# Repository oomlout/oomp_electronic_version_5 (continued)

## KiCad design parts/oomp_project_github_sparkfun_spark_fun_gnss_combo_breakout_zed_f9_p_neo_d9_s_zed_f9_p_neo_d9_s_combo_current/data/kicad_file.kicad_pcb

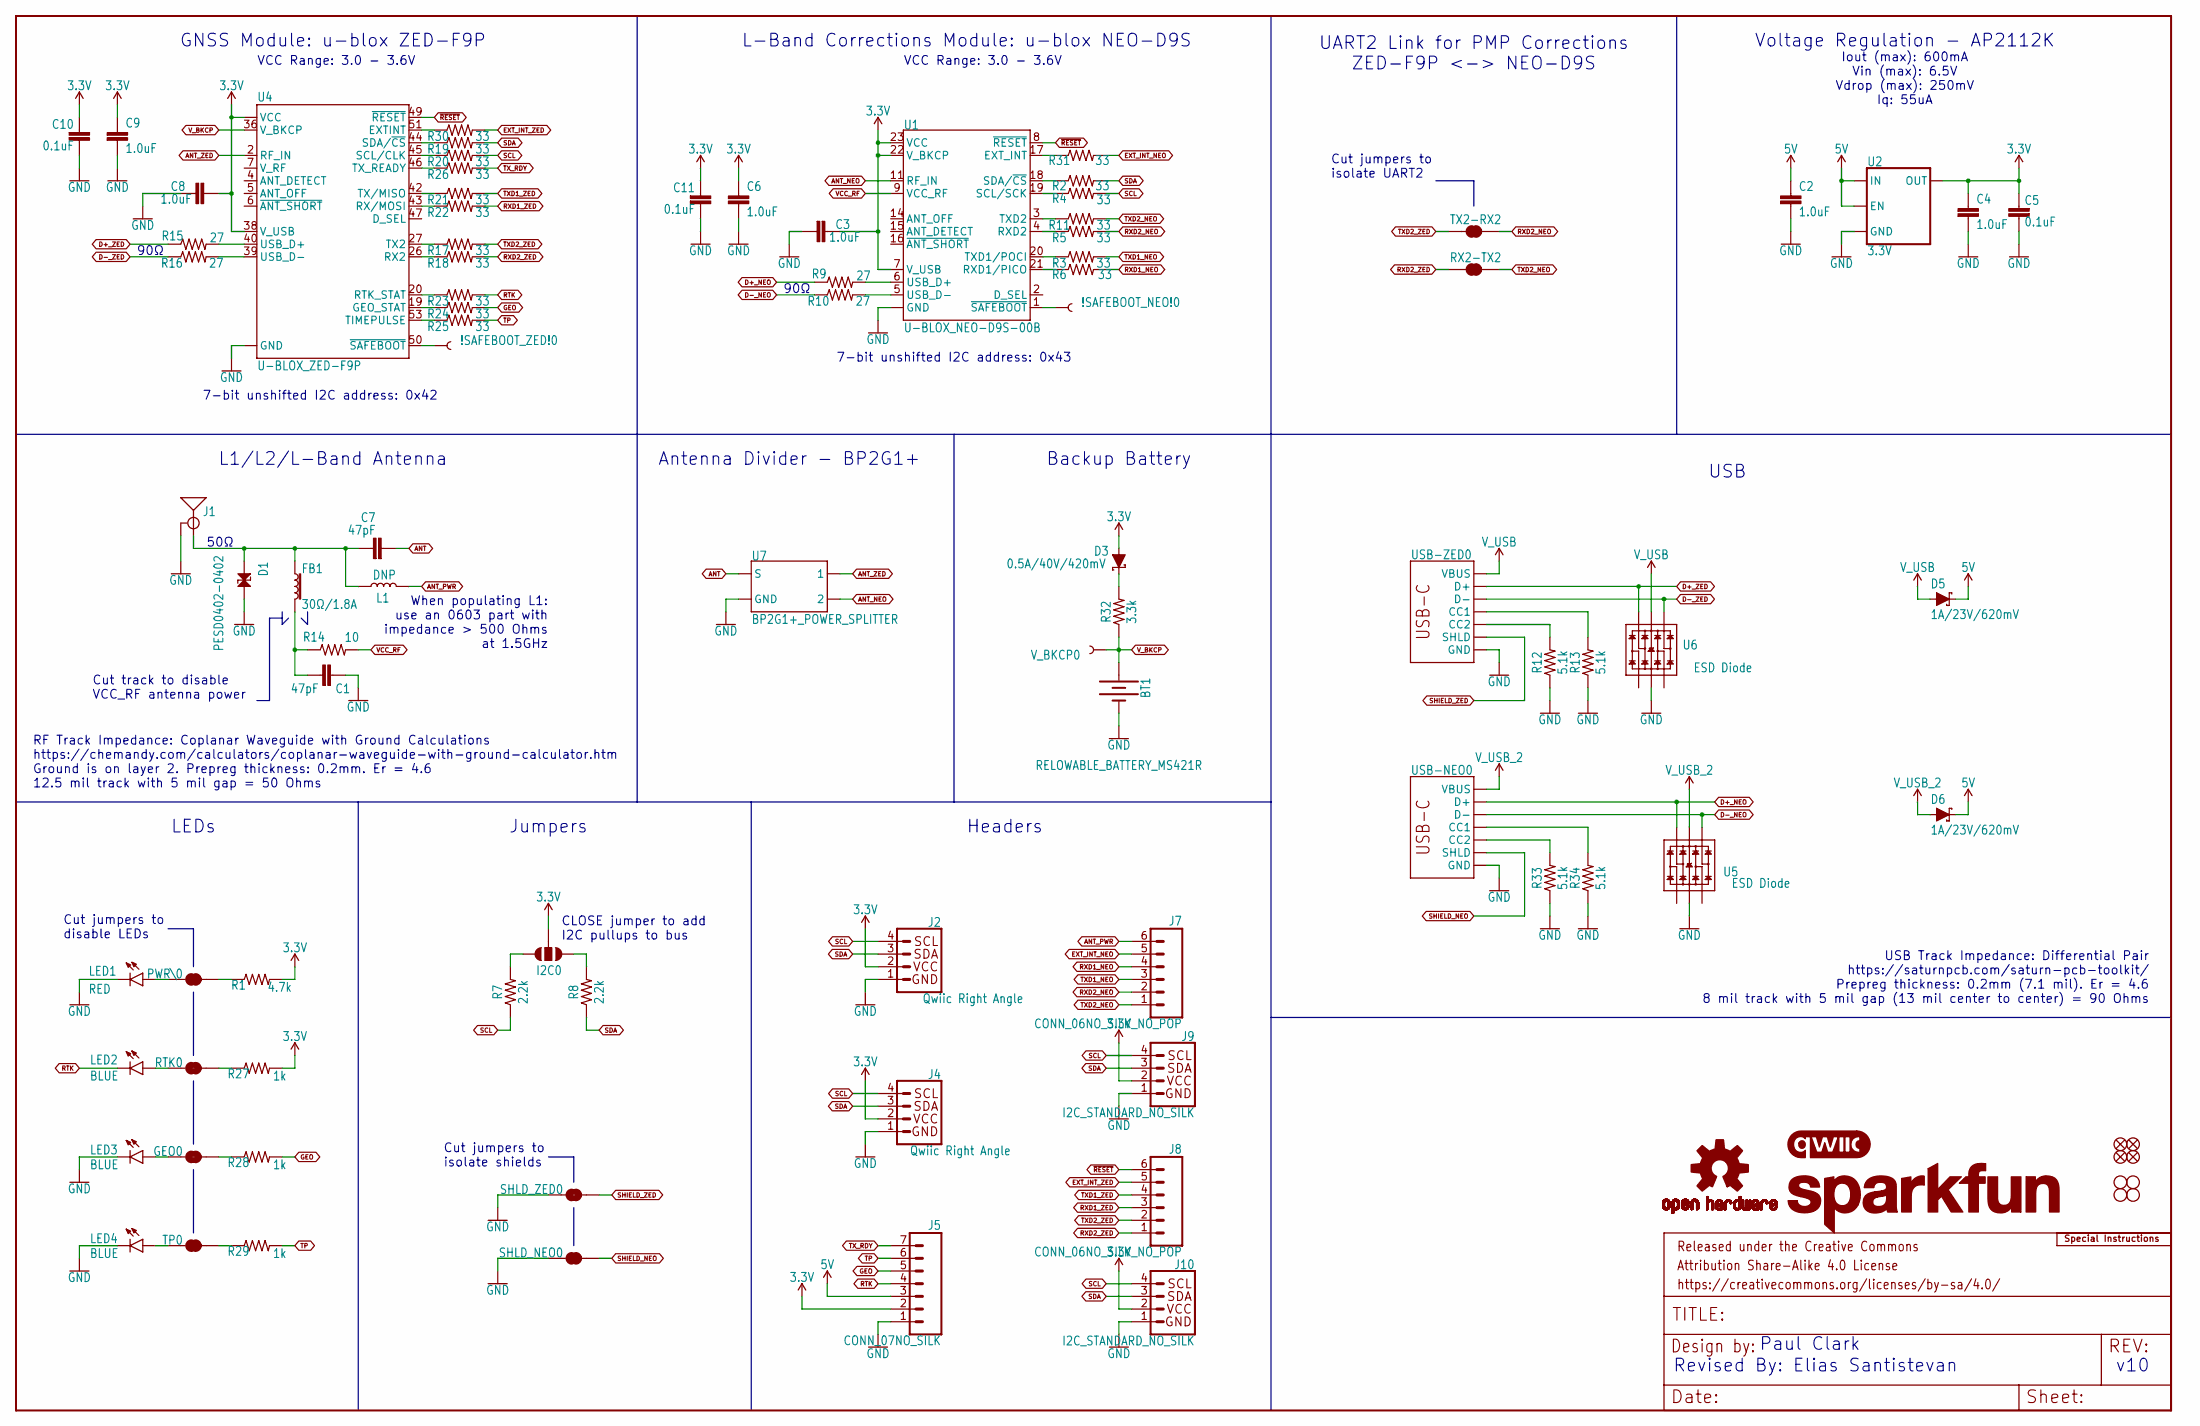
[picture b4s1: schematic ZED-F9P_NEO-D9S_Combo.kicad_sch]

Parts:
!SAFEBOOT_NEO!0: TEST-POINTPOGO_PTH; 1X01_NO_SILK
!SAFEBOOT_ZED!0: TEST-POINTPOGO_PTH; 1X01_NO_SILK
BT1: RELOWABLE_BATTERY_MS421R; MS421R_IV03E
C1, C7: 47pF; 0603
C2, C3, C4, C6, C8, C9: 1.0uF; 0603
C5, C10, C11: 0.1uF; 0603
D1: PESD0402-0402; 0402; MOUSE_PART 650-PESD0402-140; DIGIKEY_PART PESD0402-140CT-ND
D3: 0.5A/40V/420mV; SOD-323
D5, D6: 1A/23V/620mV; SOD-323
FB1: 30Ω/1.8A; 0603
FRAME2: FRAME-LEDGER; CREATIVE_COMMONS
GEO0: JUMPER-SMT_2_NC_TRACE_SILK; SMT-JUMPER_2_NC_TRACE_SILK
I2C0: JUMPER-SMT_3_NO_SILK; SMT-JUMPER_3_NO_SILK
J1: ANTENNA-SMA-GROUNDEDEDGE_SMA; SMA-EDGE
J2, J4: Qwiic Right Angle; JST04_1MM_RA
J5: CONN_07NO_SILK; 1X07_NO_SILK
J7, J8: CONN_06NO_SILK_NO_POP; 1X06_NO_SILK
J9, J10: I2C_STANDARD_NO_SILK; 1X04_NO_SILK
JP21, JP61, JP71, JP81: FIDUCIALUFIDUCIAL; MICRO-FIDUCIAL
JP31, JP41, JP91, JP101: STAND-OFF
L1: DNP; 0603_NO-CREAM
LED1: RED; LED-0603
LED2, LED3, LED4: BLUE; LED-0603
LOGO2: SFE_LOGO_NAME.1_INCH; SFE_LOGO_NAME_.1
LOGO3: QWIIC_LOGO_5MM; QWIIC_5MM
LOGO4: OSHW-LOGOS; OSHW-LOGO-S
LOGO5: SPECIAL_INSTRUCTIONS-ORDERING; ORDERING_INSTRUCTIONS
PWR\0: JUMPER-SMT_2_NC_TRACE_SILK; SMT-JUMPER_2_NC_TRACE_SILK
R1: 4.7k; 0603
R2, R3, R4, R5, R6, R11, R17, R18, R19, R20, R21, R22, R23, R24, R25, R26, R30, R31: 33; 0603
R7, R8: 2.2k; 0603
R9, R10, R15, R16: 27; 0603
R12, R13, R33, R34: 5.1k; 0603
R14: 10; 0603
R27, R28, R29: 1k; 0603
R32: 3.3k; 0603
RTK0: JUMPER-SMT_2_NC_TRACE_SILK; SMT-JUMPER_2_NC_TRACE_SILK
RX2-TX2: JUMPER-SMT_2_NC_TRACE_SILK; SMT-JUMPER_2_NC_TRACE_SILK
SHLD_NEO0: JUMPER-SMT_2_NC_TRACE_SILK; SMT-JUMPER_2_NC_TRACE_SILK
SHLD_ZED0: JUMPER-SMT_2_NC_TRACE_SILK; SMT-JUMPER_2_NC_TRACE_SILK
TP0: JUMPER-SMT_2_NC_TRACE_SILK; SMT-JUMPER_2_NC_TRACE_SILK
TX2-RX2: JUMPER-SMT_2_NC_TRACE_SILK; SMT-JUMPER_2_NC_TRACE_SILK
U1: U-BLOX_NEO-D9S-00B; NEO-M9N_M8T_M8U_D9S
U2: 3.3V; SOT23-5
U4: U-BLOX_ZED-F9P; ZED-F9P
U5, U6: ESD Diode; SOT-23-6
U7: BP2G1+_POWER_SPLITTER; XX21
USB-NEO0: USB Female Type C Connector; USB-C-16P_4LAYER-PADS
USB-ZED0: USB Female Type C Connector; USB-C-16P_4LAYER-PADS
V_BKCP0: TEST-POINT3X5; PAD.03X.05

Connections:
3.3V: C3.1, C4.1, C5.2, C6.1, C8.2, C9.1, C10.2, C11.2, D3.A, I2C0.2, J2.2, J4.2, J5.2, J9.2, J10.2, R1.2, R27.2, U1.7 (V_USB), U1.22 (V_BKCP), U1.23 (VCC), U2.5 (OUT), U4.33 (VCC), U4.34 (VCC), U4.38 (V_USB)
5V: C2.1, D5.C, D6.C, J5.3, U2.1 (IN), U2.3 (EN)
ANT: C7.2, U7.2 (S)
ANT_NEO: U1.11 (RF_IN), U7.5 (2)
ANT_PWR: J7.6, L1.2
ANT_VCC: C1.1, FB1.2, R14.1
ANT_ZED: U4.2 (RF_IN), U7.8 (1)
D+_NEO: R9.1, U5.6 (IO4), USB-NEO0.A6 (D+), USB-NEO0.B6 (D+)
D+_ZED: R15.1, U6.6 (IO4), USB-ZED0.A6 (D+), USB-ZED0.B6 (D+)
D-_NEO: R10.1, U5.4 (IO3), USB-NEO0.A7 (D-), USB-NEO0.B7 (D-)
D-_ZED: R16.1, U6.4 (IO3), USB-ZED0.A7 (D-), USB-ZED0.B7 (D-)
EXT_INT_NEO: J7.5, R31.2
EXT_INT_ZED: J8.5, R30.2
GEO: J5.5, R24.2, R28.2
GND: BT1.-, C1.2, C2.2, C3.2, C4.2, C5.1, C6.2, C8.1, C9.2, C10.1, C11.1, D1.2, J1.GND@0 (GND), J1.GND@1 (GND), J1.GND@2 (GND), J1.GND@3 (GND), J2.1, J4.1, J5.1, J9.1, J10.1, LED1.C, LED3.C, LED4.C, R12.1, R13.1, R33.1, R34.1, SHLD_NEO0.1, SHLD_ZED0.1, U1.10 (GND), U1.12 (GND), U1.13 (GND), U1.24 (GND), U2.2 (GND), U4.1 (GND), U4.3 (GND), U4.12 (GND), U4.14 (GND), U4.32 (GND), U4.37 (GND), U4.41 (GND), U4.48 (GND), U4.55 (GND), U4.56 (GND), U4.57 (GND), U4.58 (GND), U4.59 (GND), U4.60 (GND), U4.61 (GND), U4.62 (GND), U4.63 (GND), U4.64 (GND), U4.65 (GND), U4.66 (GND), U4.67 (GND), U4.68 (GND), U4.69 (GND), U4.70 (GND), U4.71 (GND), U4.72 (GND), U4.73 (GND), U4.74 (GND), U4.75 (GND), U4.76 (GND), U4.77 (GND), U4.78 (GND), U4.79 (GND), U4.80 (GND), U4.81 (GND), U4.82 (GND), U4.83 (GND), U4.84 (GND), U4.85 (GND), U4.86 (GND), U4.87 (GND), U4.88 (GND), U4.89 (GND), U4.90 (GND), U4.91 (GND), U4.92 (GND), U4.93 (GND), U4.94 (GND), U4.95 (GND), U4.96 (GND), U4.97 (GND), U4.98 (GND), U4.99 (GND), U4.100 (GND), U4.101 (GND), U4.102 (GND), U5.2 (VSS), U6.2 (VSS), U7.1 (GND), U7.3 (GND), U7.4 (GND), U7.6 (GND), U7.7 (GND), USB-NEO0.GND, USB-NEO0.GND2 (GND), USB-ZED0.GND, USB-ZED0.GND2 (GND)
unnamed: PWR\0.2, R1.1
unnamed: R3.1, U1.20 (TXD1/POCI)
unnamed: R2.1, U1.18 (SDA/~CS)
unnamed: R4.1, U1.19 (SCL/SCK)
unnamed: I2C0.1, R8.2
unnamed: R6.1, U1.21 (RXD1/PICO)
unnamed: R12.2, USB-ZED0.B5 (CC2)
unnamed: I2C0.3, R7.2
unnamed: R13.2, USB-ZED0.A5 (CC1)
unnamed: LED1.A, PWR\0.1
unnamed: R9.2, U1.6 (USB_D+)
unnamed: R10.2, U1.5 (USB_D-)
unnamed: D3.C, R32.2
unnamed: R11.1, U1.3 (TXD2)
unnamed: R5.1, U1.4 (RXD2)
unnamed: R15.2, U4.40 (USB_D+)
unnamed: R16.2, U4.39 (USB_D-)
unnamed: R19.1, U4.44 (SDA/~CS)
unnamed: R20.1, U4.45 (SCL/CLK)
unnamed: R21.1, U4.42 (TX/MISO)
unnamed: R22.1, U4.43 (RX/MOSI)
unnamed: R26.1, U4.46 (TX_READY)
unnamed: LED2.A, RTK0.1
unnamed: R17.1, U4.27 (TX2)
unnamed: R18.1, U4.26 (RX2)
unnamed: GEO0.1, LED3.A
unnamed: LED4.A, TP0.1
unnamed: R27.1, RTK0.2
unnamed: GEO0.2, R28.1
unnamed: R29.1, TP0.2
unnamed: R30.1, U4.51 (EXTINT)
unnamed: R31.1, U1.17 (EXT_INT)
unnamed: R33.2, USB-NEO0.B5 (CC2)
unnamed: R34.2, USB-NEO0.A5 (CC1)
unnamed: R23.1, U4.20 (RTK_STAT)
unnamed: R24.1, U4.19 (GEO_STAT)
unnamed: R25.1, U4.53 (TIMEPULSE)
RTK: J5.4, LED2.C, R23.2
RXD1_NEO: J7.4, R6.2
RXD1_ZED: J8.3, R22.2
RXD2_NEO: J7.2, R5.2, TX2-RX2.2
RXD2_ZED: J8.1, R18.2, RX2-TX2.1
SCL: J2.4, J4.4, J9.4, J10.4, R4.2, R7.1, R20.2
SDA: J2.3, J4.3, J9.3, J10.3, R2.2, R8.1, R19.2
SHIELD_NEO: SHLD_NEO0.2, USB-NEO0.SHLD1 (SHLD), USB-NEO0.SHLD2 (SHLD), USB-NEO0.SHLD3 (SHLD), USB-NEO0.SHLD4 (SHLD)
SHIELD_ZED: SHLD_ZED0.2, USB-ZED0.SHLD1 (SHLD), USB-ZED0.SHLD2 (SHLD), USB-ZED0.SHLD3 (SHLD), USB-ZED0.SHLD4 (SHLD)
SMA: C7.1, D1.1, FB1.1, J1.SIG (SIGNAL), L1.1
TP: J5.6, R25.2, R29.2
TXD1_NEO: J7.3, R3.2
TXD1_ZED: J8.4, R21.2
TXD2_NEO: J7.1, R11.2, RX2-TX2.2
TXD2_ZED: J8.2, R17.2, TX2-RX2.1
TX_RDY: J5.7, R26.2
VCC_RF: R14.2, U1.9 (VCC_RF)
V_BKCP: BT1.+, R32.1, U4.36 (V_BKCP), V_BKCP0.1
V_USB: D5.A, U6.5 (VCC), USB-ZED0.VBUS1 (VBUS), USB-ZED0.VBUS2 (VBUS)
V_USB_2: D6.A, U5.5 (VCC), USB-NEO0.VBUS1 (VBUS), USB-NEO0.VBUS2 (VBUS)
~RESET: J8.6, U1.8 (~RESET), U4.49 (~RESET)
~SAFEBOOT_NEO: !SAFEBOOT_NEO!0.1, U1.1 (~SAFEBOOT)
~SAFEBOOT_ZED: !SAFEBOOT_ZED!0.1, U4.50 (~SAFEBOOT)

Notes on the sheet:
Cut jumpers to isolate shields
CLOSE jumper to add I2C pullups to bus
Paul Clark
v10
Headers
Jumpers
When populating L1: use an 0603 part with impedance > 500 Ohms at 1.5GHz
7-bit unshifted I2C address: 0x42
L-Band Corrections Module: u-blox NEO-D9S
50Ω
UART2 Link for PMP Corrections ZED-F9P <-> NEO-D9S
90Ω
Revised By: Elias Santistevan
VCC Range: 3.0 - 3.6V
Voltage Regulation - AP2112K
Iout (max): 600mA Vin (max): 6.5V Vdrop (max): 250mV Iq: 55uA
Backup Battery
Cut jumpers to isolate UART2
7-bit unshifted I2C address: 0x43
Antenna Divider - BP2G1+
LEDs
USB Track Impedance: Differential Pair https://saturnpcb.com/saturn-pcb-toolkit/ Prepreg thickness: 0.2mm (7.1 mil). Er = 4.6 8 mil track with 5 mil gap (13 mil center to center) = 90 Ohms
RF Track Impedance: Coplanar Waveguide with Ground Calculations https://chemandy.com/calculators/coplanar-waveguide-with-ground-calculator.htm Ground is on layer 2. Prepreg thickness: 0.2mm. Er = 4.6 12.5 mil track with 5 mil gap = 50 Ohms
Cut track to disable VCC_RF antenna power
USB
L1/L2/L-Band Antenna
Cut jumpers to disable LEDs
GNSS Module: u-blox ZED-F9P

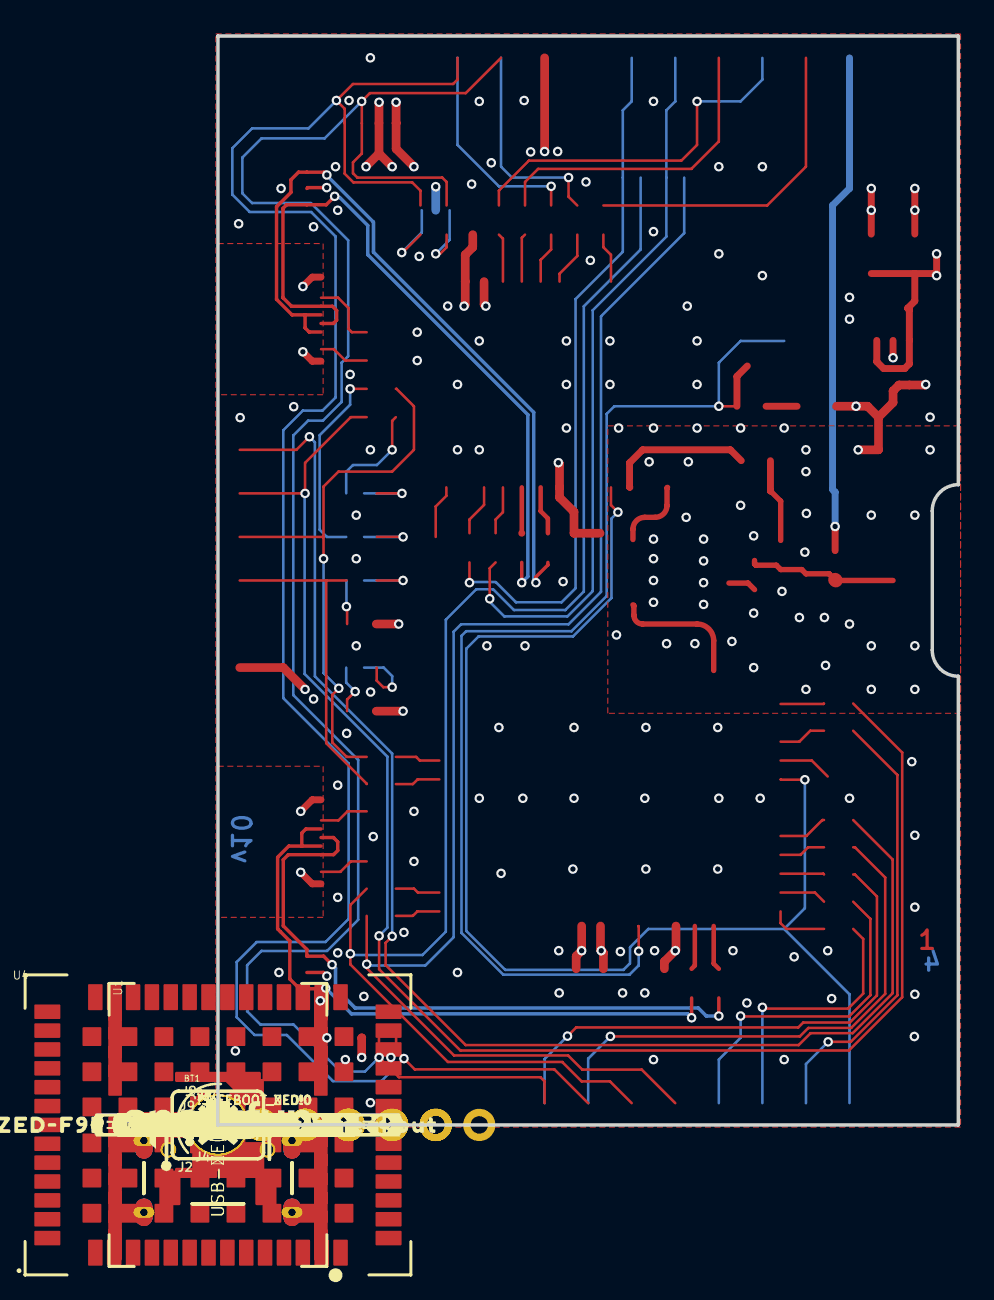
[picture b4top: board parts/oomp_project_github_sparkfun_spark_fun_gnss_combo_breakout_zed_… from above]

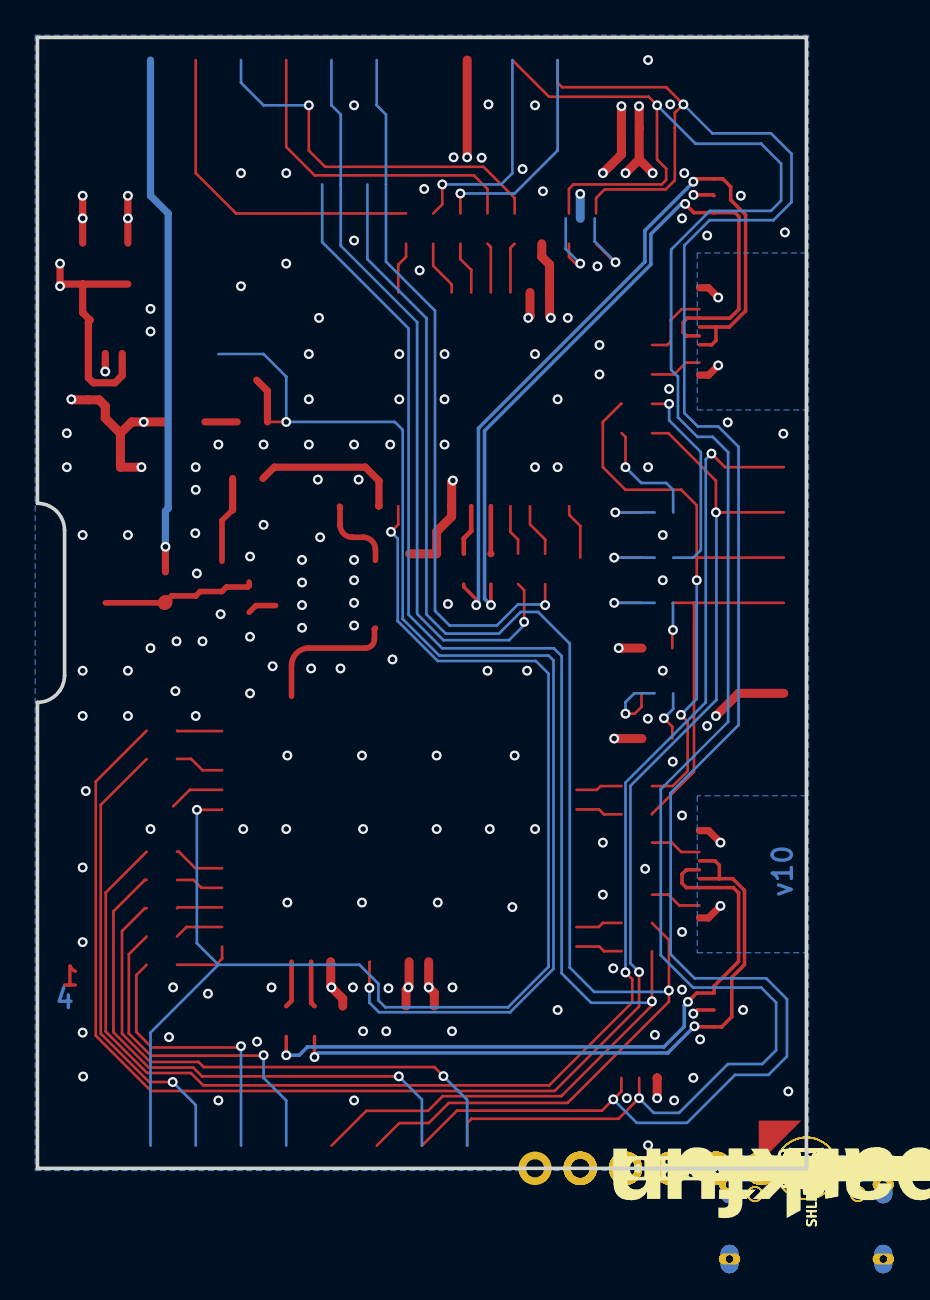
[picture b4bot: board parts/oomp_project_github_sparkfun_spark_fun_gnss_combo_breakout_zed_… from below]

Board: 4 copper layers, 43.2 x 63.5 mm, 179 parts (60 on the bottom side), 75 nets.

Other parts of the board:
LOGO1: OSHW-LOGOS; OSHW-LOGO-S
LOGO6: QWIIC_LOGO_5MM; QWIIC_5MM
U$1, U$2, U$3: #GND#0
U$4, U$5, U$6: #GND#1
U$7: #SHLD_ZED#15
U$8, U$10: #SDA#0
U$9, U$13: #SCL#0
U$11, U$12: #SDA#1
U$14: L#BAND18
U$15, U$30: #SCL#1
U$16: #RTK#0
U$17: #RTK#1
U$18: #GEO#0
U$19: #GEO#1
U$20: #5V#0
U$21: #5V#6
U$22, U$23, U$56: #3V3#0
U$24, U$25, U$70: #3V3#4
U$26: #TP#0
U$27: #TP#1
U$28: #TX_RDY#0
U$29: #TX_RDY#1
U$31, U$39, U$40: #TX2#0
U$32, U$34, U$35: #RX2#0
U$33: L1#L218
U$36, U$37: #RX2#3
U$41, U$42: #TX2#3
U$43, U$44: #RX1#0
U$45: ##RESET##0
U$46: ##RESET##1
U$47: #EXT_INT#0
U$48: #EXT_INT_ZED#0
U$49, U$50: #RX1#2
U$51, U$57: #TX1#0
U$52: #I�C#0
U$53: #SHLD_NEO#12
U$54: ANTENNA18
U$55: NEO#D9S16
U$58: #ANT_PWR#0
U$59: #ANT_PWR#1
U$60, U$61: #TX1#2
U$62: #EXT_INT_NEO#0
U$63: #EXT_INT_NEO#1
U$64: COMBO16
U$65: ZED#F9P10
U$66: NEO#D9S10
U$67: BREAKOUT17
U$68: SFE_LOGO_NAME_.2
U$69: #PWR#0
U$71: ##SAFEBOOT#_NEO#13
U$72: ##SAFEBOOT#_ZED#14
U$73: OPEN_JUMPERS13
U$74: TO_ISOLATE_UART214
U$75: ZED#F9P_NEO#D9S_COMBO_BREAKOUT0
U$76: DEF_ADDRESS#_12
U$78: ZED#F9P16
U$79: NEO#D9S#13
U$80: ZED#F9P#13
U$81: 0X4313
U$82: 0X4213

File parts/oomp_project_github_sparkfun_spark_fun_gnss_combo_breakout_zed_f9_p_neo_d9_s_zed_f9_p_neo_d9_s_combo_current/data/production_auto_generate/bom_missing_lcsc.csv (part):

Designator,Comment,Footprint,OOMP ID,Reason
!SAFEBOOT_NEO!0,TEST-POINTPOGO_PTH,ZED-F9P_NEO-D9S_Combo-import-fps:1X01_NO_SILK,,No verified LCSC part number
!SAFEBOOT_ZED!0,TEST-POINTPOGO_PTH,ZED-F9P_NEO-D9S_Combo-import-fps:1X01_NO_SILK,,No verified LCSC part number
BT1,RELOWABLE_BATTERY_MS421R,ZED-F9P_NEO-D9S_Combo-import-fps:MS421R_IV03E,,No verified LCSC part number
D1,PESD0402-0402,ZED-F9P_NEO-D9S_Combo-import-fps:0402,,No verified LCSC part number
D3,0.5A/40V/420mV,ZED-F9P_NEO-D9S_Combo-import-fps:SOD-323,,No verified LCSC part number
D5,1A/23V/620mV,ZED-F9P_NEO-D9S_Combo-import-fps:SOD-323,,No verified LCSC part number
D6,1A/23V/620mV,ZED-F9P_NEO-D9S_Combo-import-fps:SOD-323,,No verified LCSC part number
FB1,30Ω/1.8A,ZED-F9P_NEO-D9S_Combo-import-fps:0603,electronic_ferrite_bead_0603_600_ohm_500_milliamp,No verified LCSC part number
FRAME2,FRAME-LEDGER,ZED-F9P_NEO-D9S_Combo-import-fps:CREATIVE_COMMONS,,No verified LCSC part number
GEO0,JUMPER-SMT_2_NC_TRACE_SILK,ZED-F9P_NEO-D9S_Combo-import-fps:SMT-JUMPER_2_NC_TRACE_SILK,,No verified LCSC part number
I2C0,JUMPER-SMT_3_NO_SILK,ZED-F9P_NEO-D9S_Combo-import-fps:SMT-JUMPER_3_NO_SILK,,No verified LCSC part number
J1,ANTENNA-SMA-GROUNDEDEDGE_SMA,ZED-F9P_NEO-D9S_Combo-import-fps:SMA-EDGE,,No verified LCSC part number
J2,Qwiic Right Angle,ZED-F9P_NEO-D9S_Combo-import-fps:JST04_1MM_RA,,No verified LCSC part number
J4,Qwiic Right Angle,ZED-F9P_NEO-D9S_Combo-import-fps:JST04_1MM_RA,,No verified LCSC part number
JP21,FIDUCIALUFIDUCIAL,ZED-F9P_NEO-D9S_Combo-import-fps:MICRO-FIDUCIAL,,No verified LCSC part number
JP61,FIDUCIALUFIDUCIAL,ZED-F9P_NEO-D9S_Combo-import-fps:MICRO-FIDUCIAL,,No verified LCSC part number
JP71,FIDUCIALUFIDUCIAL,ZED-F9P_NEO-D9S_Combo-import-fps:MICRO-FIDUCIAL,,No verified LCSC part number
JP81,FIDUCIALUFIDUCIAL,ZED-F9P_NEO-D9S_Combo-import-fps:MICRO-FIDUCIAL,,No verified LCSC part number
L1,DNP,ZED-F9P_NEO-D9S_Combo-import-fps:0603_NO-CREAM,,No verified LCSC part number
LED1,RED,ZED-F9P_NEO-D9S_Combo-import-fps:LED-0603,electronic_led_0603_red,No verified LCSC part number
LED2,BLUE,ZED-F9P_NEO-D9S_Combo-import-fps:LED-0603,electronic_led_0603_blue,No verified LCSC part number
LED3,BLUE,ZED-F9P_NEO-D9S_Combo-import-fps:LED-0603,electronic_led_0603_blue,No verified LCSC part number
LED4,BLUE,ZED-F9P_NEO-D9S_Combo-import-fps:LED-0603,electronic_led_0603_blue,No verified LCSC part number
PWR\0,JUMPER-SMT_2_NC_TRACE_SILK,ZED-F9P_NEO-D9S_Combo-import-fps:SMT-JUMPER_2_NC_TRACE_SILK,,No verified LCSC part number
RTK0,JUMPER-SMT_2_NC_TRACE_SILK,ZED-F9P_NEO-D9S_Combo-import-fps:SMT-JUMPER_2_NC_TRACE_SILK,,No verified LCSC part number
RX2-TX2,JUMPER-SMT_2_NC_TRACE_SILK,ZED-F9P_NEO-D9S_Combo-import-fps:SMT-JUMPER_2_NC_TRACE_SILK,,No verified LCSC part number
SHLD_NEO0,JUMPER-SMT_2_NC_TRACE_SILK,ZED-F9P_NEO-D9S_Combo-import-fps:SMT-JUMPER_2_NC_TRACE_SILK,,No verified LCSC part number
SHLD_ZED0,JUMPER-SMT_2_NC_TRACE_SILK,ZED-F9P_NEO-D9S_Combo-import-fps:SMT-JUMPER_2_NC_TRACE_SILK,,No verified LCSC part number
TP0,JUMPER-SMT_2_NC_TRACE_SILK,ZED-F9P_NEO-D9S_Combo-import-fps:SMT-JUMPER_2_NC_TRACE_SILK,,No verified LCSC part number
TX2-RX2,JUMPER-SMT_2_NC_TRACE_SILK,ZED-F9P_NEO-D9S_Combo-import-fps:SMT-JUMPER_2_NC_TRACE_SILK,,No verified LCSC part number
U1,U-BLOX_NEO-D9S-00B,ZED-F9P_NEO-D9S_Combo-import-fps:NEO-M9N_M8T_M8U_D9S,,No verified LCSC part number
U2,3.3V,ZED-F9P_NEO-D9S_Combo-import-fps:SOT23-5,,No verified LCSC part number
U4,U-BLOX_ZED-F9P,ZED-F9P_NEO-D9S_Combo-import-fps:ZED-F9P,,No verified LCSC part number
U5,ESD Diode,ZED-F9P_NEO-D9S_Combo-import-fps:SOT-23-6,,No verified LCSC part number
U6,ESD Diode,ZED-F9P_NEO-D9S_Combo-import-fps:SOT-23-6,,No verified LCSC part number
U7,BP2G1+_POWER_SPLITTER,ZED-F9P_NEO-D9S_Combo-import-fps:XX21,,No verified LCSC part number
U$1,,ZED-F9P_NEO-D9S_Combo-import-fps:#GND#0,,No verified LCSC part number
U$2,,ZED-F9P_NEO-D9S_Combo-import-fps:#GND#0,,No verified LCSC part number
U$3,,ZED-F9P_NEO-D9S_Combo-import-fps:#GND#0,,No verified LCSC part number
U$4,,ZED-F9P_NEO-D9S_Combo-import-fps:#GND#1,,No verified LCSC part number
U$5,,ZED-F9P_NEO-D9S_Combo-import-fps:#GND#1,,No verified LCSC part number
U$6,,ZED-F9P_NEO-D9S_Combo-import-fps:#GND#1,,No verified LCSC part number
U$7,,ZED-F9P_NEO-D9S_Combo-import-fps:#SHLD_ZED#15,,No verified LCSC part number
U$8,,ZED-F9P_NEO-D9S_Combo-import-fps:#SDA#0,,No verified LCSC part number
U$9,,ZED-F9P_NEO-D9S_Combo-import-fps:#SCL#0,,No verified LCSC part number
U$10,,ZED-F9P_NEO-D9S_Combo-import-fps:#SDA#0,,No verified LCSC part number
U$11,,ZED-F9P_NEO-D9S_Combo-import-fps:#SDA#1,,No verified LCSC part number
U$12,,ZED-F9P_NEO-D9S_Combo-import-fps:#SDA#1,,No verified LCSC part number
U$13,,ZED-F9P_NEO-D9S_Combo-import-fps:#SCL#0,,No verified LCSC part number
U$14,,ZED-F9P_NEO-D9S_Combo-import-fps:L#BAND18,,No verified LCSC part number
U$15,,ZED-F9P_NEO-D9S_Combo-import-fps:#SCL#1,,No verified LCSC part number
U$16,,ZED-F9P_NEO-D9S_Combo-import-fps:#RTK#0,,No verified LCSC part number
U$17,,ZED-F9P_NEO-D9S_Combo-import-fps:#RTK#1,,No verified LCSC part number
U$18,,ZED-F9P_NEO-D9S_Combo-import-fps:#GEO#0,,No verified LCSC part number
U$19,,ZED-F9P_NEO-D9S_Combo-import-fps:#GEO#1,,No verified LCSC part number
U$20,,ZED-F9P_NEO-D9S_Combo-import-fps:#5V#0,,No verified LCSC part number
U$21,,ZED-F9P_NEO-D9S_Combo-import-fps:#5V#6,,No verified LCSC part number
U$22,,ZED-F9P_NEO-D9S_Combo-import-fps:#3V3#0,,No verified LCSC part number
U$23,,ZED-F9P_NEO-D9S_Combo-import-fps:#3V3#0,,No verified LCSC part number
U$24,,ZED-F9P_NEO-D9S_Combo-import-fps:#3V3#4,,No verified LCSC part number
U$25,,ZED-F9P_NEO-D9S_Combo-import-fps:#3V3#4,,No verified LCSC part number
U$26,,ZED-F9P_NEO-D9S_Combo-import-fps:#TP#0,,No verified LCSC part number
U$27,,ZED-F9P_NEO-D9S_Combo-import-fps:#TP#1,,No verified LCSC part number
U$28,,ZED-F9P_NEO-D9S_Combo-import-fps:#TX_RDY#0,,No verified LCSC part number
U$29,,ZED-F9P_NEO-D9S_Combo-import-fps:#TX_RDY#1,,No verified LCSC part number
U$30,,ZED-F9P_NEO-D9S_Combo-import-fps:#SCL#1,,No verified LCSC part number
U$31,,ZED-F9P_NEO-D9S_Combo-import-fps:#TX2#0,,No verified LCSC part number
U$32,,ZED-F9P_NEO-D9S_Combo-import-fps:#RX2#0,,No verified LCSC part number
U$33,,ZED-F9P_NEO-D9S_Combo-import-fps:L1#L218,,No verified LCSC part number
U$34,,ZED-F9P_NEO-D9S_Combo-import-fps:#RX2#0,,No verified LCSC part number
U$35,,ZED-F9P_NEO-D9S_Combo-import-fps:#RX2#0,,No verified LCSC part number
U$36,,ZED-F9P_NEO-D9S_Combo-import-fps:#RX2#3,,No verified LCSC part number
U$37,,ZED-F9P_NEO-D9S_Combo-import-fps:#RX2#3,,No verified LCSC part number
U$39,,ZED-F9P_NEO-D9S_Combo-import-fps:#TX2#0,,No verified LCSC part number
U$40,,ZED-F9P_NEO-D9S_Combo-import-fps:#TX2#0,,No verified LCSC part number
U$41,,ZED-F9P_NEO-D9S_Combo-import-fps:#TX2#3,,No verified LCSC part number
U$42,,ZED-F9P_NEO-D9S_Combo-import-fps:#TX2#3,,No verified LCSC part number
U$43,,ZED-F9P_NEO-D9S_Combo-import-fps:#RX1#0,,No verified LCSC part number
U$44,,ZED-F9P_NEO-D9S_Combo-import-fps:#RX1#0,,No verified LCSC part number
U$45,,ZED-F9P_NEO-D9S_Combo-import-fps:##RESET##0,,No verified LCSC part number
U$46,,ZED-F9P_NEO-D9S_Combo-import-fps:##RESET##1,,No verified LCSC part number
U$47,,ZED-F9P_NEO-D9S_Combo-import-fps:#EXT_INT#0,,No verified LCSC part number
U$48,,ZED-F9P_NEO-D9S_Combo-import-fps:#EXT_INT_ZED#0,,No verified LCSC part number
U$49,,ZED-F9P_NEO-D9S_Combo-import-fps:#RX1#2,,No verified LCSC part number
U$50,,ZED-F9P_NEO-D9S_Combo-import-fps:#RX1#2,,No verified LCSC part number
U$51,,ZED-F9P_NEO-D9S_Combo-import-fps:#TX1#0,,No verified LCSC part number
U$52,,ZED-F9P_NEO-D9S_Combo-import-fps:#I�C#0,,No verified LCSC part number
U$53,,ZED-F9P_NEO-D9S_Combo-import-fps:#SHLD_NEO#12,,No verified LCSC part number
U$54,,ZED-F9P_NEO-D9S_Combo-import-fps:ANTENNA18,,No verified LCSC part number
U$55,,ZED-F9P_NEO-D9S_Combo-import-fps:NEO#D9S16,,No verified LCSC part number
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
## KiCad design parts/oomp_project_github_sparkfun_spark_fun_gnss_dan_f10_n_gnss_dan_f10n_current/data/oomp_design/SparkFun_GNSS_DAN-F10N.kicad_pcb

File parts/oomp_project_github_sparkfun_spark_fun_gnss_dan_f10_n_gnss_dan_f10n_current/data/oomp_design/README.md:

# OOMP KiCad design copy

Open `SparkFun_GNSS_DAN-F10N.kicad_pro` (or the `.kicad_pcb` / `.kicad_sch`) in KiCad. Local OOMP libraries are under `libraries/`. Original inputs are preserved in [../original/](../original/).

Only verified unchanged installed KiCad defaults were renamed. Modified, custom, unmatched and unavailable items remain unchanged. Soldering variants are never swapped during conversion. Existing pad coordinates, nets and UUIDs are preserved.

See [conversion_report.yaml](conversion_report.yaml) for every conversion and skip. Copy this directory before editing; regeneration refuses to overwrite edited design files.

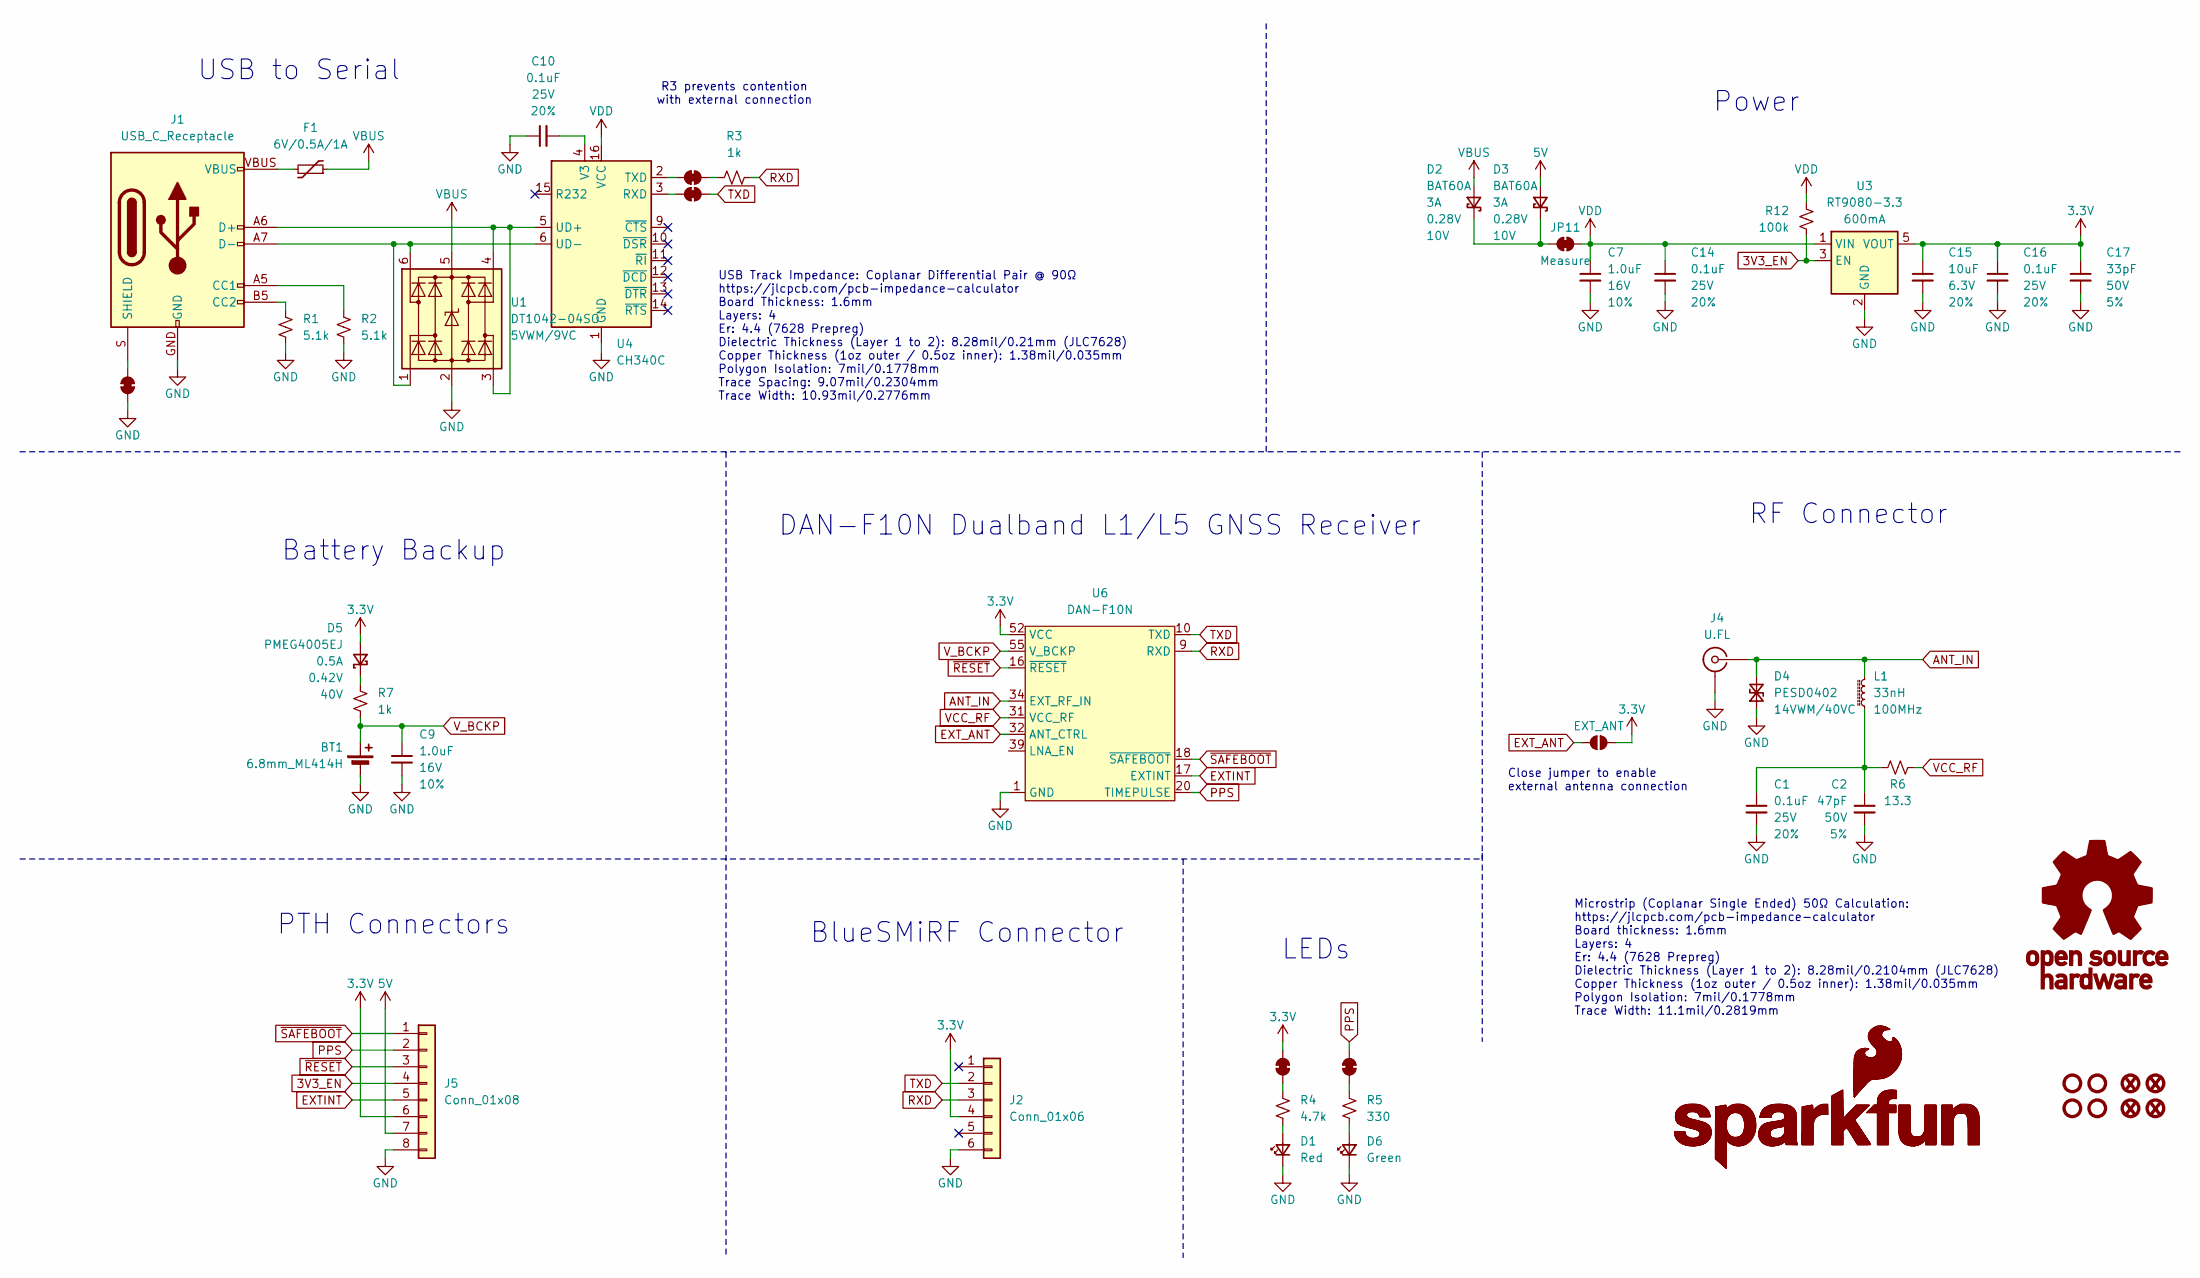
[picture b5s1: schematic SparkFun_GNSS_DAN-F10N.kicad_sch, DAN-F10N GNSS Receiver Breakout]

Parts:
BT1: 6.8mm_ML414H; ML414H_IV01E
C1, C10, C14, C16: 0.1uF; C_0603_1608Metric; Voltage 25V; Tolerance 20%
C2: 47pF; C_0603_1608Metric; Voltage 50V; Tolerance 5%
C7, C9: 1.0uF; C_0603_1608Metric; Voltage 16V; Tolerance 10%
C15: 10uF; C_0603_1608Metric; Voltage 6.3V; Tolerance 20%
C17: 33pF; C_0603_1608Metric; Voltage 50V; Tolerance 5%
D1: Red; LED_0603_1608Metric_Red
D2, D3: BAT60A; SOD-323
D4: PESD0402; C_0402_1005Metric; Rating 14VWM/40VC
D5: PMEG4005EJ; SOD-323
D6: Green; LED_1206_Bottom_Green
F1: 6V/0.5A/1A; 0805
FID1, FID2, FID3, FID4: Fiducial_0.5mm; Fiducial_0.5mm_Mask1mm
G1: OSHW_Logo; Creative_Commons_License
G3: SparkFun_Logo
G5: SparkFun_Logo; SparkFun_Logo_8mm
J1: USB_C_Receptacle; USB-C_16
J2: Conn_01x06; 1x06
J4: U.FL
J5: Conn_01x08; 1x08
JP1: EXT_ANT; Jumper_2_NO
JP2, JP3, JP7, JP9, JP10: Jumper_2_NC_Trace
JP11: Measure; Jumper_2_PTH_SMD_Combo-NC
L1: 33nH; C_0603_1608Metric
R1, R2: 5.1k; R_0603_1608Metric
R3, R7: 1k; R_0603_1608Metric
R4: 4.7k; R_0603_1608Metric
R5: 330; R_0603_1608Metric
R6: 13.3; R_2512_6332Metric
R12: 100k; R_0603_1608Metric
ST1, ST2, ST3, ST4: Standoff
U1: DT1042-04SO; SOT23-6; Rating 5VWM/9VC
U3: RT9080-3.3; SOT23-5
U4: CH340C; SO-16
U6: DAN-F10N; u-blox_DAN-F10N

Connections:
3.3V: C15.1, C16.1, C17.1, D5.2 (A), J2.4, J5.6, JP1.1 (A), JP2.2 (B), U3.5 (VOUT), U6.52 (VCC), U6.53 (VCC)
3V3_EN: J5.4, R12.1, U3.3 (EN)
5V: D3.2 (A), J5.7
ANT_IN: D4.2 (A2), J4.1 (In), L1.2, U6.34 (EXT_RF_IN)
EXTINT: J5.5, U6.17 (EXTINT)
EXT_ANT: JP1.2 (B), U6.32 (ANT_CTRL)
GND: BT1.-, C1.2, C2.2, C7.2, C9.2, C10.1, C14.2, C15.2, C16.2, C17.2, D1.1 (K), D4.1 (A1), D6.1 (K), J1.GND, J2.6, J4.2 (Ext), J5.8, JP7.1 (A), R1.1, R2.1, U1.2 (GND), U3.2 (GND), U4.1 (GND), U6.1 (GND), U6.2 (GND), U6.3 (GND), U6.4 (GND), U6.5 (GND), U6.6 (GND), U6.7 (GND), U6.8 (GND), U6.13 (GND), U6.14 (GND), U6.15 (GND), U6.19 (GND), U6.21 (GND), U6.22 (GND), U6.23 (GND), U6.26 (GND), U6.27 (GND), U6.28 (GND), U6.29 (GND), U6.30 (GND), U6.33 (GND), U6.35 (GND), U6.37 (GND), U6.38 (GND), U6.40 (GND), U6.41 (GND), U6.42 (GND), U6.43 (GND), U6.44 (GND), U6.47 (GND), U6.48 (GND), U6.49 (GND), U6.50 (GND), U6.51 (GND), U6.54 (GND), U6.56 (GND), U6.57 (GND)
unnamed: C1.1, C2.1, L1.1, R6.2
unnamed: D1.2 (A), R4.1
unnamed: D2.1 (K), D3.1 (K), JP11.1 (A)
unnamed: D5.1 (K), R7.2
unnamed: D6.2 (A), R5.1
unnamed: F1.2, J1.VBUS
unnamed: J1.A5 (CC1), R2.2
unnamed: J1.B5 (CC2), R1.2
unnamed: J1.S (SHIELD), JP7.2 (B)
unnamed: JP2.1 (A), R4.2
unnamed: JP3.1 (A), R5.2
unnamed: JP9.1 (A), U4.2 (TXD)
unnamed: JP9.2 (B), R3.2
unnamed: JP10.1 (A), U4.3 (RXD)
unnamed: J1.A7 (D-), J1.B7 (D-), U1.1 (I/O1), U1.6 (I/O4), U4.6 (UD-)
unnamed: J1.A6 (D+), J1.B6 (D+), U1.3 (I/O2), U1.4 (I/O3), U4.5 (UD+)
unnamed: C10.2, U4.4 (V3)
PPS: J5.2, JP3.2 (B), U6.20 (TIMEPULSE)
RXD: J2.3, R3.1, U6.9 (RXD)
TXD: J2.2, JP10.2 (B), U6.10 (TXD)
VBUS: D2.2 (A), F1.1, U1.5 (VCC)
VCC_RF: R6.1, U6.31 (VCC_RF)
VDD: C7.1, C14.1, JP11.2 (B), R12.2, U3.1 (VIN), U4.16 (VCC)
V_BCKP: BT1.+, C9.1, R7.1, U6.55 (V_BCKP)
~RESET: J5.3, U6.16 (~RESET)
~SAFEBOOT: J5.1, U6.18 (~SAFEBOOT)

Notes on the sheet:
Close jumper to enable external antenna connection
R3 prevents contention with external connection
Microstrip (Coplanar Single Ended) 50Ω Calculation: https://jlcpcb.com/pcb-impedance-calculator Board thickness: 1.6mm Layers: 4 Er: 4.4 (7628 Prepreg) Dielectric Thickness (Layer 1 to 2): 8.28mil/0.2104mm (JLC7628) Copper Thickness (1oz outer / 0.5oz inner): 1.38mil/0.035mm Polygon Isolation: 7mil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
USB Track Impedance: Coplanar Differential Pair @ 90Ω https://jlcpcb.com/pcb-impedance-calculator Board Thickness: 1.6mm Layers: 4 Er: 4.4 (7628 Prepreg) Dielectric Thickness (Layer 1 to 2): 8.28mil/0.21mm (JLC7628) Copper Thickness (1oz outer / 0.5oz inner): 1.38mil/0.035mm Polygon Isolation: 7mil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
RF Connector
BlueSMiRF Connector
LEDs
DAN-F10N Dualband L1/L5 GNSS Receiver
USB to Serial
Battery Backup
Power
PTH Connectors
